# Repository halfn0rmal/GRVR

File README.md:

# GRVR
An open source cnc driver shield for grbl.

KiCad project.

The spindle drive needs to be inverted in the grbl library as it does not support it in settings yet.
 Open up config.h in the grbl library.
 Comment out #define VARIABLE_SPINDLE
 uncomment #define INVERT_SPINDLE_ENABLE_PIN

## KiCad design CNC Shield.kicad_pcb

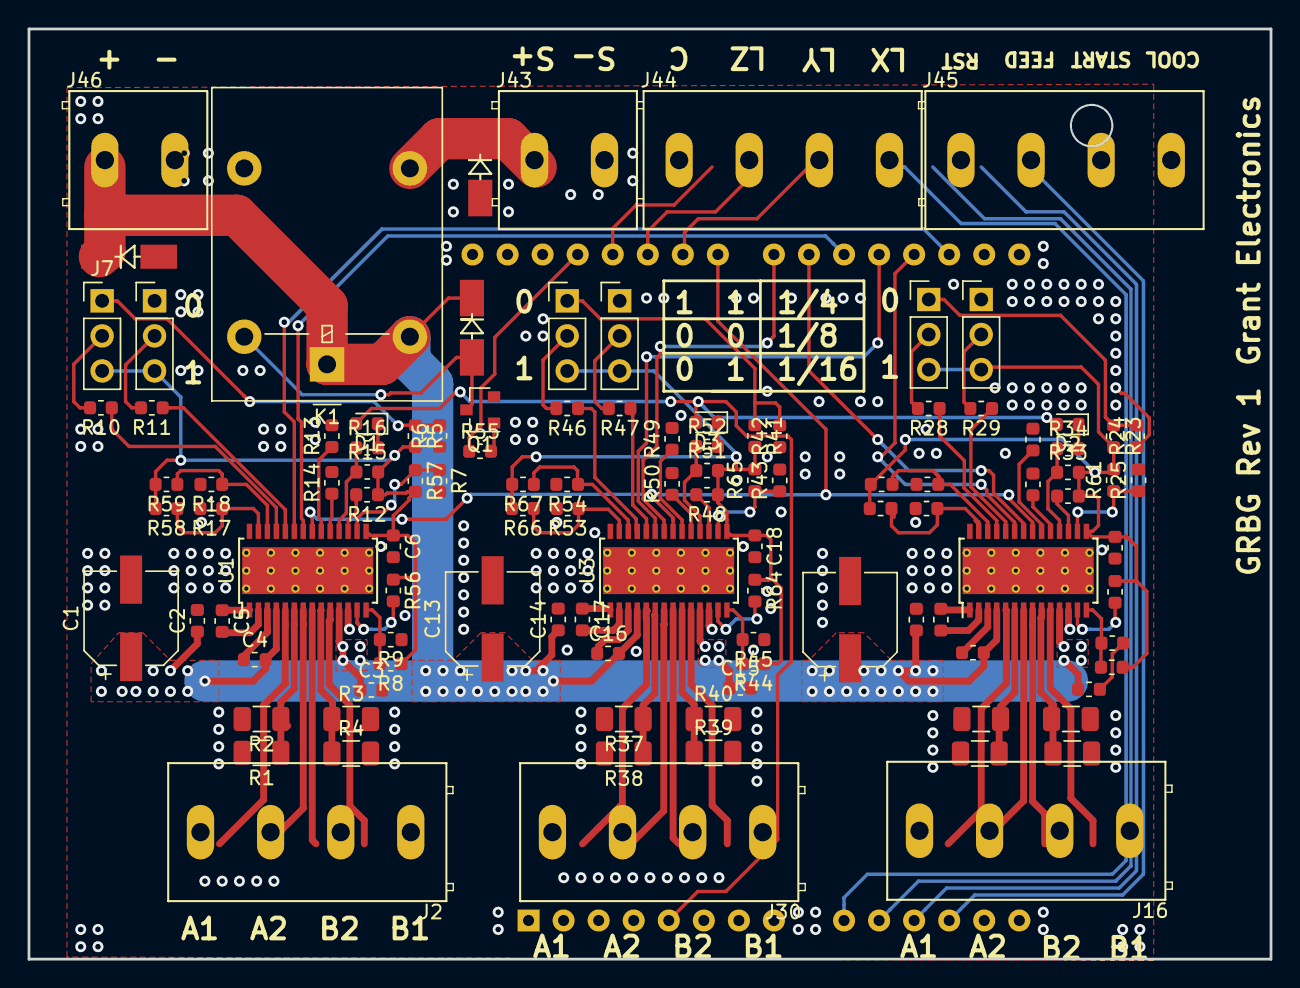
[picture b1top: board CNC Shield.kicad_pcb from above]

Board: 2 copper layers, 90.0 x 67.4 mm, 110 parts (1 on the bottom side), 96 nets.

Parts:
A1: Arduino_UNO_R2
C1, C7, C13: 100uF; CP_Elec_6.3x5.4
C2, C3, C5, C8, C9, C11, C14, C15, C17: 100nF; C_0603_1608Metric
C4, C6, C10, C12, C16, C18: 470nF; C_0603_1608Metric
D1, D2, D3: LED_Small; LED_0603_1608Metric
D4, D5, D6: S1M; DO-214AC
J2: X MOTOR; Connector_4T-BLK
J7, J21, J35: M0_JUMPER; PinHeader_1x03_P2.54mm_Vertical
J8, J22, J36: M1_JUMPER; PinHeader_1x03_P2.54mm_Vertical
J16: Y MOTOR; Connector_4T-BLK
J30: Z MOTOR; Connector_4T-BLK
J43: SPINDLE; Connector_2T-BLK
J44: LIMITS; Connector_4T-BLK
J45: CONTROLS; Connector_4T-BLK
J46: 24V In; Connector_2T-BLK
K1: G5LE-1; Relay_SPDT_Omron-G5LE-1
Q1: BC847; SOT-23
R1, R2, R3, R4, R19, R20, R21, R22, R37, R38, R39, R40: 0.5R; R_1206_3216Metric
R5, R7, R9, R10, R11, R12, R13, R14, R15, R17, R18, R23, R25, R27, R28, R29, R30, R31, R32, R33, R35, R36, R41, R43, R45, R46, R47, R48, R49, R50, R51, R53, R54, R55, R56, R60, R64, R67: 10K; R_0603_1608Metric
R6, R24, R42: 5K; R_0603_1608Metric
R8, R26, R44: 22K; R_0603_1608Metric
R16, R34, R52: 150R; R_0603_1608Metric
R57, R58, R59, R61, R62, R63, R65, R66: NC; R_0603_1608Metric
U1, U2, U3: DRV8880; HTSSOP-28-1EP_4.4x9.7mm_P0.65mm_EP3.4x9.5mm_ThermalVias

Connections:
+5V: A1.5, D1.2, D2.2, D3.2
+24V: C1.1, C2.1, C3.1, C4.2, C7.1, C8.1, C9.1, C10.2, C13.1, C14.1, C15.1, C16.2, D4.1, D6.1, J46.1, K1.1, K1.2, U1.4, U1.11, U2.4, U2.11, U3.4, U3.11
/3P3X: C6.1, J7.3, J8.3, R5.2, R8.1, R12.1, R15.2, R56.1, R57.2, R58.2, R59.2, U1.15
/AISEN: R1.1, R2.1, U1.6
/ATE: R56.2, U1.13
/BISEN: R3.1, R4.1, U1.9
/DECAY0: R13.1, U1.20
/DECAY1: R14.1, U1.19
/M0: R10.1, U1.25
/M1: R11.1, U1.24
/TOFF: R7.1, R57.1, U1.16
/TRQ0: R17.1, R58.1, U1.27
/TRQ1: R18.1, R59.1, U1.26
/Y Axis Driver/3P3Y: C12.1, J21.3, J22.3, R23.2, R26.1, R30.1, R33.2, R60.1, R61.2, R62.2, R63.2, U2.15
/Y Axis Driver/AISEN: R19.1, R20.1, U2.6
/Y Axis Driver/ATE: R60.2, U2.13
/Y Axis Driver/BISEN: R21.1, R22.1, U2.9
/Y Axis Driver/DECAY0: R31.1, U2.20
/Y Axis Driver/DECAY1: R32.1, U2.19
/Y Axis Driver/M0: R28.1, U2.25
/Y Axis Driver/M1: R29.1, U2.24
/Y Axis Driver/TOFF: R25.1, R61.1, U2.16
/Y Axis Driver/TRQ0: R35.1, R62.1, U2.27
/Y Axis Driver/TRQ1: R36.1, R63.1, U2.26
/Y Axis Driver/Z: J21.1, R23.1, R24.2
/Z: J7.1, R5.1, R6.2
/Z Axis Driver/3P3Z: C18.1, J35.3, J36.3, R41.2, R44.1, R48.1, R51.2, R64.1, R65.2, R66.2, R67.2, U3.15
/Z Axis Driver/AISEN: R37.1, R38.1, U3.6
/Z Axis Driver/ATE: R64.2, U3.13
/Z Axis Driver/BISEN: R39.1, R40.1, U3.9
/Z Axis Driver/DECAY0: R49.1, U3.20
/Z Axis Driver/DECAY1: R50.1, U3.19
/Z Axis Driver/M0: R46.1, U3.25
/Z Axis Driver/M1: R47.1, U3.24
/Z Axis Driver/TOFF: R43.1, R65.1, U3.16
/Z Axis Driver/TRQ0: R53.1, R66.1, U3.27
/Z Axis Driver/TRQ1: R54.1, R67.1, U3.26
/Z Axis Driver/Z: J35.1, R41.1, R42.2
DIR_X: A1.20, U1.22
DIR_Y: A1.21, U2.22
DIR_Z: A1.22, U3.22
GND: A1.6, A1.7, A1.29, C1.2, C2.2, C3.2, C6.2, C7.2, C8.2, C9.2, C12.2, C13.2, C14.2, C15.2, C18.2, D5.2, D6.2, J8.1, J22.1, J36.1, J43.2, J44.1, J46.2, Q1.2, R1.2, R2.2, R3.2, R4.2, R6.1, R7.2, R9.1, R13.2, R14.2, R17.2, R18.2, R19.2, R20.2, R21.2, R22.2, R24.1, R25.2, R27.1, R31.2, R32.2, R35.2, R36.2, R37.2, R38.2, R39.2, R40.2, R42.1, R43.2, R45.1, R49.2, R50.2, R53.2, R54.2, U1.12, U1.28, U1.29, U2.12, U2.28, U2.29, U3.12, U3.28, U3.29
unnamed: A1.9, J45.1
unnamed: A1.10, J45.2
unnamed: A1.11, J45.3
unnamed: A1.12, J45.4
unnamed: A1.24, J44.4
unnamed: A1.25, J44.3
unnamed: A1.26, J44.2
unnamed: C4.1, U1.3
unnamed: C5.1, U1.1
unnamed: C5.2, U1.2
unnamed: C10.1, U2.3
unnamed: C11.1, U2.1
unnamed: C11.2, U2.2
unnamed: C16.1, U3.3
unnamed: C17.1, U3.1
unnamed: C17.2, U3.2
unnamed: D1.1, R16.2
unnamed: D2.1, R34.2
unnamed: D3.1, R52.2
unnamed: D4.2, K1.5, Q1.3
unnamed: D5.1, J43.1, K1.3
unnamed: J2.1, U1.10
unnamed: J2.2, U1.8
unnamed: J2.3, U1.7
unnamed: J2.4, U1.5
unnamed: J7.2, R10.2
unnamed: J8.2, R11.2
unnamed: J16.1, U2.10
unnamed: J16.2, U2.8
unnamed: J16.3, U2.7
unnamed: J16.4, U2.5
unnamed: J21.2, R28.2
unnamed: J22.2, R29.2
unnamed: J30.1, U3.10
unnamed: J30.2, U3.8
unnamed: J30.3, U3.7
unnamed: J30.4, U3.5
unnamed: J35.2, R46.2
unnamed: J36.2, R47.2
unnamed: Q1.1, R55.2
unnamed: R8.2, R9.2, U1.14
unnamed: R12.2, U1.17
unnamed: R26.2, R27.2, U2.14
unnamed: R30.2, U2.17
unnamed: R44.2, R45.2, U3.14
unnamed: R48.2, U3.17
SPINDLE_ENABLE: A1.27, R55.1
STEPPER_ENABLE: A1.23, U1.21, U2.21, U3.21
STEP_X: A1.17, U1.23
STEP_Y: A1.18, U2.23
STEP_Z: A1.19, U3.23
X_FAULT: R15.1, R16.1, U1.18
Y_FAULT: R33.1, R34.1, U2.18
Z_FAULT: R51.1, R52.1, U3.18
